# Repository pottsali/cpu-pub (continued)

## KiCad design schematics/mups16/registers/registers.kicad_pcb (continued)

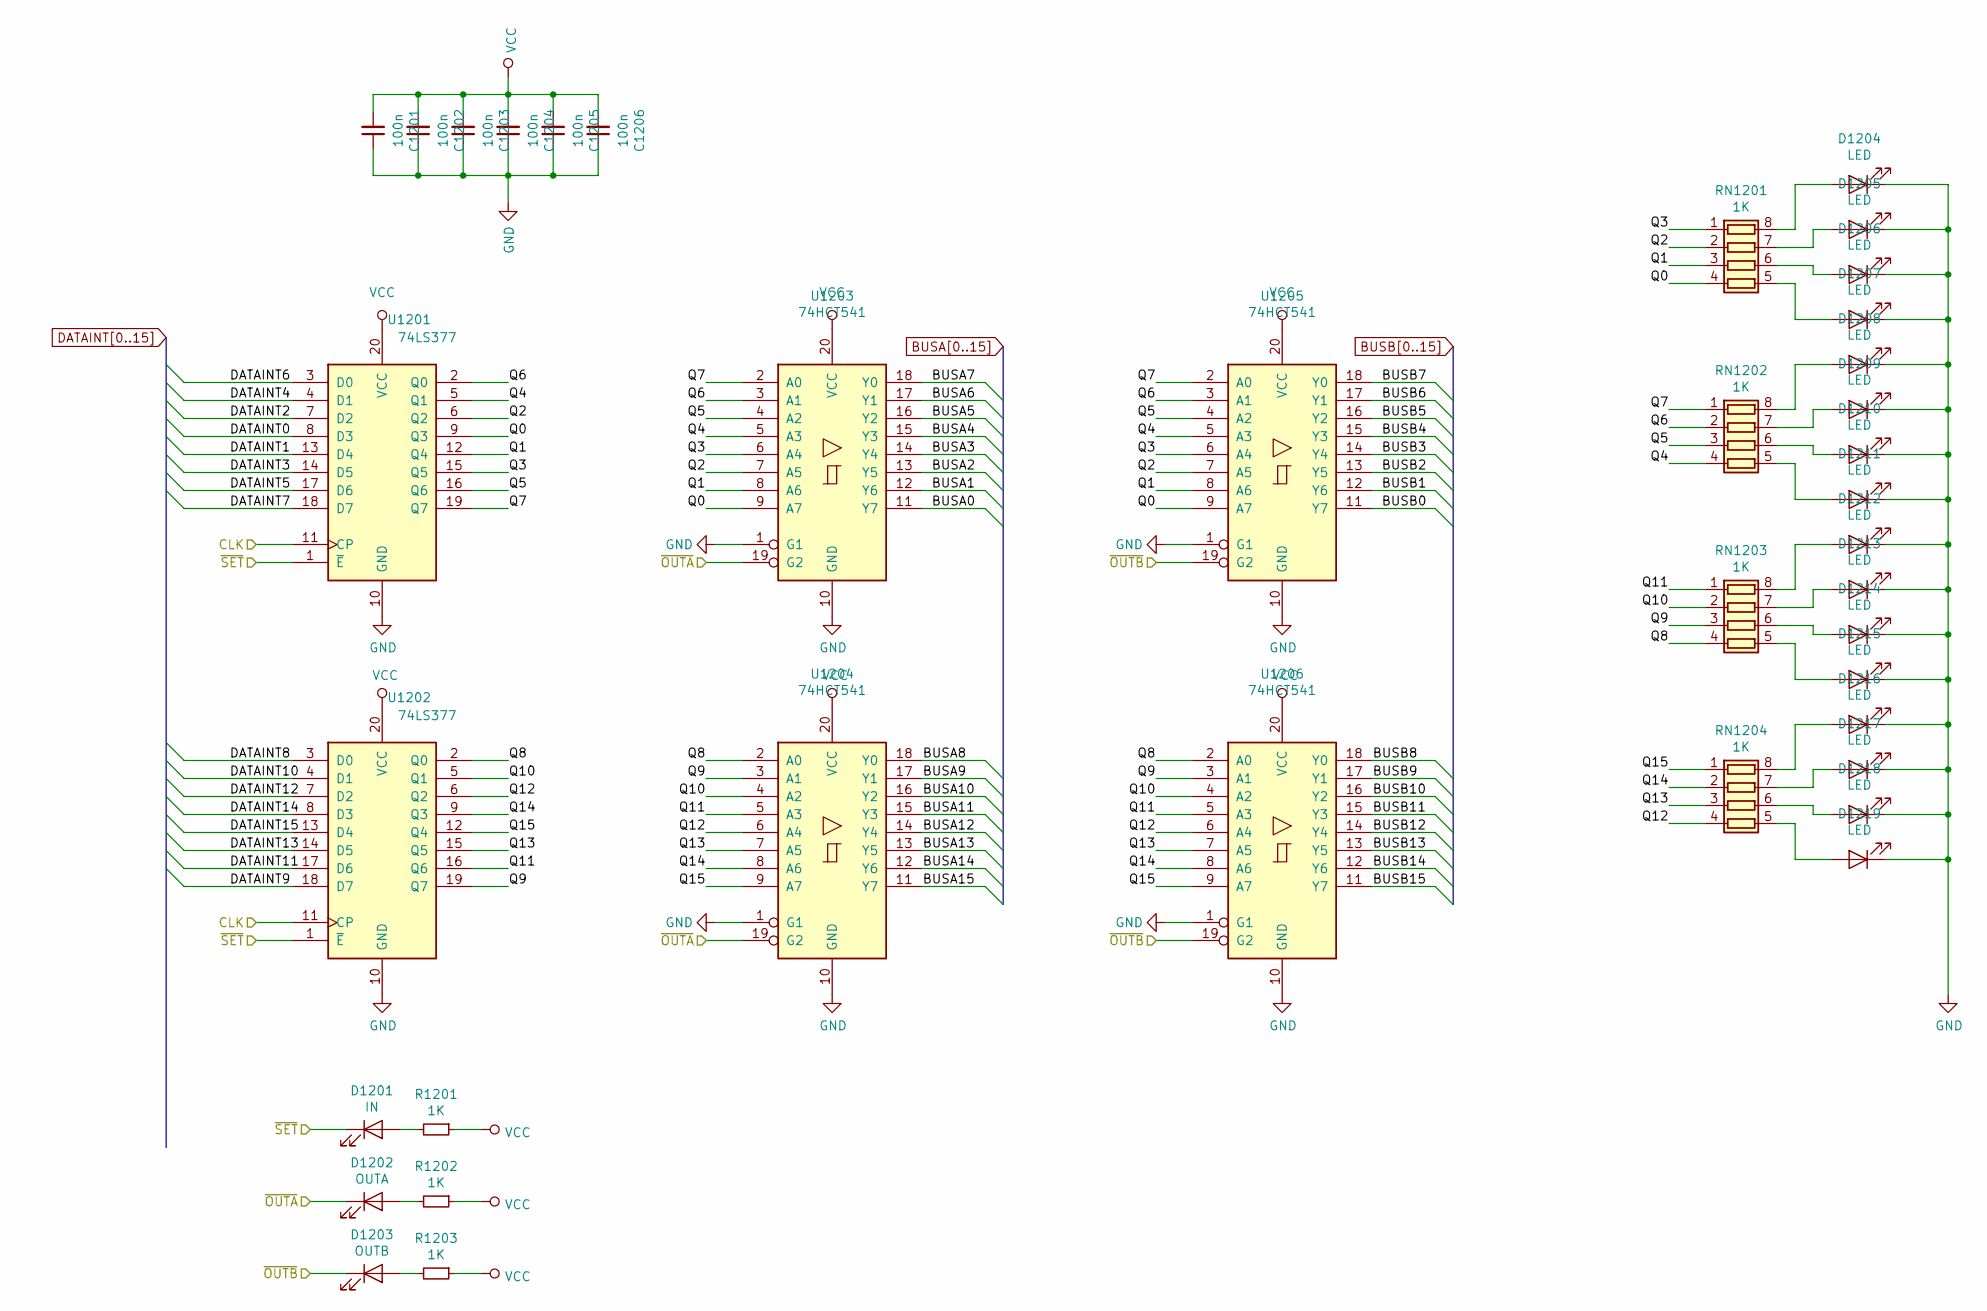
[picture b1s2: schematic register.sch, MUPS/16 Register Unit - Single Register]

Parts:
C201, C202, C203, C204, C205, C206: 100n; C_0805_2012Metric
D201: IN; LED_0805_2012Metric
D202: OUTA; LED_0805_2012Metric
D203: OUTB; LED_0805_2012Metric
D204, D205, D206, D207, D208, D209, D210, D211, D212, D213, D214, D215, D216, D217, D218, D219: LED; LED_0805_2012Metric
R201, R202, R203: 1K; R_0805_2012Metric
RN201, RN202, RN203, RN204: 1K; R_Array_Convex_4x1206
U201, U202: 74LS377; SOIC-20W_7.5x12.8mm_P1.27mm
U203, U204, U205, U206: 74HCT541; SOIC-20W_7.5x12.8mm_P1.27mm

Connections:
/CLK: U201.11 (CP), U202.11 (CP); also elsewhere on the board
/OUTA1: D202.1 (K), U203.19 (G2), U204.19 (G2); also elsewhere on the board
/OUTB1: D203.1 (K), U205.19 (G2), U206.19 (G2); also elsewhere on the board
/SETF1: D201.1 (K), U201.1 (~E), U202.1 (~E); also elsewhere on the board
/r1/Q0: RN201.4 (R4.1), U201.9 (Q3), U203.9 (A7), U205.9 (A7)
/r1/Q1: RN201.3 (R3.1), U201.12 (Q4), U203.8 (A6), U205.8 (A6)
/r1/Q2: RN201.2 (R2.1), U201.6 (Q2), U203.7 (A5), U205.7 (A5)
/r1/Q3: RN201.1 (R1.1), U201.15 (Q5), U203.6 (A4), U205.6 (A4)
/r1/Q4: RN202.4 (R4.1), U201.5 (Q1), U203.5 (A3), U205.5 (A3)
/r1/Q5: RN202.3 (R3.1), U201.16 (Q6), U203.4 (A2), U205.4 (A2)
/r1/Q6: RN202.2 (R2.1), U201.2 (Q0), U203.3 (A1), U205.3 (A1)
/r1/Q7: RN202.1 (R1.1), U201.19 (Q7), U203.2 (A0), U205.2 (A0)
/r1/Q8: RN203.4 (R4.1), U202.2 (Q0), U204.2 (A0), U206.2 (A0)
/r1/Q9: RN203.3 (R3.1), U202.19 (Q7), U204.3 (A1), U206.3 (A1)
/r1/Q10: RN203.2 (R2.1), U202.5 (Q1), U204.4 (A2), U206.4 (A2)
/r1/Q11: RN203.1 (R1.1), U202.16 (Q6), U204.5 (A3), U206.5 (A3)
/r1/Q12: RN204.4 (R4.1), U202.6 (Q2), U204.6 (A4), U206.6 (A4)
/r1/Q13: RN204.3 (R3.1), U202.15 (Q5), U204.7 (A5), U206.7 (A5)
/r1/Q14: RN204.2 (R2.1), U202.9 (Q3), U204.8 (A6), U206.8 (A6)
/r1/Q15: RN204.1 (R1.1), U202.12 (Q4), U204.9 (A7), U206.9 (A7)
BUSA0: U203.11 (Y7); also elsewhere on the board
BUSA1: U203.12 (Y6); also elsewhere on the board
BUSA2: U203.13 (Y5); also elsewhere on the board
BUSA3: U203.14 (Y4); also elsewhere on the board
BUSA4: U203.15 (Y3); also elsewhere on the board
BUSA5: U203.16 (Y2); also elsewhere on the board
BUSA6: U203.17 (Y1); also elsewhere on the board
BUSA7: U203.18 (Y0); also elsewhere on the board
BUSA8: U204.18 (Y0); also elsewhere on the board
BUSA9: U204.17 (Y1); also elsewhere on the board
BUSA10: U204.16 (Y2); also elsewhere on the board
BUSA11: U204.15 (Y3); also elsewhere on the board
BUSA12: U204.14 (Y4); also elsewhere on the board
BUSA13: U204.13 (Y5); also elsewhere on the board
BUSA14: U204.12 (Y6); also elsewhere on the board
BUSA15: U204.11 (Y7); also elsewhere on the board
BUSB0: U205.11 (Y7); also elsewhere on the board
BUSB1: U205.12 (Y6); also elsewhere on the board
BUSB2: U205.13 (Y5); also elsewhere on the board
BUSB3: U205.14 (Y4); also elsewhere on the board
BUSB4: U205.15 (Y3); also elsewhere on the board
BUSB5: U205.16 (Y2); also elsewhere on the board
BUSB6: U205.17 (Y1); also elsewhere on the board
BUSB7: U205.18 (Y0); also elsewhere on the board
BUSB8: U206.18 (Y0); also elsewhere on the board
BUSB9: U206.17 (Y1); also elsewhere on the board
BUSB10: U206.16 (Y2); also elsewhere on the board
BUSB11: U206.15 (Y3); also elsewhere on the board
BUSB12: U206.14 (Y4); also elsewhere on the board
BUSB13: U206.13 (Y5); also elsewhere on the board
BUSB14: U206.12 (Y6); also elsewhere on the board
BUSB15: U206.11 (Y7); also elsewhere on the board
DATAINT0: U201.8 (D3); also elsewhere on the board
DATAINT1: U201.13 (D4); also elsewhere on the board
DATAINT2: U201.7 (D2); also elsewhere on the board
DATAINT3: U201.14 (D5); also elsewhere on the board
DATAINT4: U201.4 (D1); also elsewhere on the board
DATAINT5: U201.17 (D6); also elsewhere on the board
DATAINT6: U201.3 (D0); also elsewhere on the board
DATAINT7: U201.18 (D7); also elsewhere on the board
DATAINT8: U202.3 (D0); also elsewhere on the board
DATAINT9: U202.18 (D7); also elsewhere on the board
DATAINT10: U202.4 (D1); also elsewhere on the board
DATAINT11: U202.17 (D6); also elsewhere on the board
DATAINT12: U202.7 (D2); also elsewhere on the board
DATAINT13: U202.14 (D5); also elsewhere on the board
DATAINT14: U202.8 (D3); also elsewhere on the board
DATAINT15: U202.13 (D4); also elsewhere on the board
GND: C201.1, C202.1, C203.1, C204.1, C205.1, C206.1, D204.1 (K), D205.1 (K), D206.1 (K), D207.1 (K), D208.1 (K), D209.1 (K), D210.1 (K), D211.1 (K), D212.1 (K), D213.1 (K), D214.1 (K), D215.1 (K), D216.1 (K), D217.1 (K), D218.1 (K), D219.1 (K), U201.10 (GND), U202.10 (GND), U203.1 (G1), U203.10 (GND), U204.1 (G1), U204.10 (GND), U205.1 (G1), U205.10 (GND), U206.1 (G1), U206.10 (GND); also elsewhere on the board
unnamed: D201.2 (A), R201.2
unnamed: D202.2 (A), R202.2
unnamed: D203.2 (A), R203.2
unnamed: D204.2 (A), RN201.8 (R1.2)
unnamed: D205.2 (A), RN201.7 (R2.2)
unnamed: D206.2 (A), RN201.6 (R3.2)
unnamed: D207.2 (A), RN201.5 (R4.2)
unnamed: D208.2 (A), RN202.8 (R1.2)
unnamed: D209.2 (A), RN202.7 (R2.2)
unnamed: D210.2 (A), RN202.6 (R3.2)
unnamed: D211.2 (A), RN202.5 (R4.2)
unnamed: D212.2 (A), RN203.8 (R1.2)
unnamed: D213.2 (A), RN203.7 (R2.2)
unnamed: D214.2 (A), RN203.6 (R3.2)
unnamed: D215.2 (A), RN203.5 (R4.2)
unnamed: D216.2 (A), RN204.8 (R1.2)
unnamed: D217.2 (A), RN204.7 (R2.2)
unnamed: D218.2 (A), RN204.6 (R3.2)
unnamed: D219.2 (A), RN204.5 (R4.2)
VCC: C201.2, C202.2, C203.2, C204.2, C205.2, C206.2, R201.1, R202.1, R203.1, U201.20 (VCC), U202.20 (VCC), U203.20 (VCC), U204.20 (VCC), U205.20 (VCC), U206.20 (VCC); also elsewhere on the board

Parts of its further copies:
C301, C302, C303, C304, C305, C306, C401, C402, C403, C404, C405, C406, C501, C502, C503, C504, C505, C506, C601, C602, C603, C604, C605, C606, C701, C702, C703, C704, C705, C706, C801, C802, C803, C804, C805, C806, C901, C902, C903, C904, C905, C906, C1001, C1002, C1003, C1004, C1005, C1006, C1101, C1102, C1103, C1104, C1105, C1106, C1201, C1202, C1203, C1204, C1205, C1206, C1301, C1302, C1303, C1304, C1305, C1306, C1401, C1402, C1403, C1404, C1405, C1406: 100n; C_0805_2012Metric
D301, D401, D501, D601, D701, D801, D901, D1001, D1101, D1201, D1301, D1401: IN; LED_0805_2012Metric
D302, D402, D502, D602, D702, D802, D902, D1002, D1102, D1202, D1302, D1402: OUTA; LED_0805_2012Metric
D303, D403, D503, D603, D703, D803, D903, D1003, D1103, D1203, D1303, D1403: OUTB; LED_0805_2012Metric
D304, D305, D306, D307, D308, D309, D310, D311, D312, D313, D314, D315, D316, D317, D318, D319, D404, D405, D406, D407, D408, D409, D410, D411, D412, D413, D414, D415, D416, D417, D418, D419, D504, D505, D506, D507, D508, D509, D510, D511, D512, D513, D514, D515, D516, D517, D518, D519, D604, D605, D606, D607, D608, D609, D610, D611, D612, D613, D614, D615, D616, D617, D618, D619, D704, D705, D706, D707, D708, D709, D710, D711, D712, D713, D714, D715, D716, D717, D718, D719, D804, D805, D806, D807, D808, D809, D810, D811, D812, D813, D814, D815, D816, D817, D818, D819, D904, D905, D906, D907, D908, D909, D910, D911, D912, D913, D914, D915, D916, D917, D918, D919, D1004, D1005, D1006, D1007, D1008, D1009, D1010, D1011, D1012, D1013, D1014, D1015, D1016, D1017, D1018, D1019, D1104, D1105, D1106, D1107, D1108, D1109, D1110, D1111, D1112, D1113, D1114, D1115, D1116, D1117, D1118, D1119, D1204, D1205, D1206, D1207, D1208, D1209, D1210, D1211, D1212, D1213, D1214, D1215, D1216, D1217, D1218, D1219, D1304, D1305, D1306, D1307, D1308, D1309, D1310, D1311, D1312, D1313, D1314, D1315, D1316, D1317, D1318, D1319, D1404, D1405, D1406, D1407, D1408, D1409, D1410, D1411, D1412, D1413, D1414, D1415, D1416, D1417, D1418, D1419: LED; LED_0805_2012Metric
R301, R302, R303, R401, R402, R403, R501, R502, R503, R601, R602, R603, R701, R702, R703, R801, R802, R803, R901, R902, R903, R1001, R1002, R1003, R1101, R1102, R1103, R1201, R1202, R1203, R1301, R1302, R1303, R1401, R1402, R1403: 1K; R_0805_2012Metric
RN301, RN302, RN303, RN304, RN401, RN402, RN403, RN404, RN501, RN502, RN503, RN504, RN601, RN602, RN603, RN604, RN701, RN702, RN703, RN704, RN801, RN802, RN803, RN804, RN901, RN902, RN903, RN904, RN1001, RN1002, RN1003, RN1004, RN1101, RN1102, RN1103, RN1104, RN1201, RN1202, RN1203, RN1204, RN1301, RN1302, RN1303, RN1304, RN1401, RN1402, RN1403, RN1404: 1K; R_Array_Convex_4x1206
U301, U302, U401, U402, U501, U502, U601, U602, U701, U702, U801, U802, U901, U902, U1001, U1002, U1101, U1102, U1201, U1202, U1301, U1302, U1401, U1402: 74LS377; SOIC-20W_7.5x12.8mm_P1.27mm
U303, U304, U305, U306, U403, U404, U405, U406, U503, U504, U505, U506, U603, U604, U605, U606, U703, U704, U705, U706, U803, U804, U805, U806, U903, U904, U905, U906, U1003, U1004, U1005, U1006, U1103, U1104, U1105, U1106, U1203, U1204, U1205, U1206, U1303, U1304, U1305, U1306, U1403, U1404, U1405, U1406: 74HCT541; SOIC-20W_7.5x12.8mm_P1.27mm

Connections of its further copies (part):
/CLK: U301.11 (CP), U302.11 (CP), U401.11 (CP), U402.11 (CP), U501.11 (CP), U502.11 (CP), U601.11 (CP), U602.11 (CP), U701.11 (CP), U702.11 (CP), U801.11 (CP), U802.11 (CP), U901.11 (CP), U902.11 (CP), U1001.11 (CP), U1002.11 (CP), U1101.11 (CP), U1102.11 (CP), U1201.11 (CP), U1202.11 (CP), U1301.11 (CP), U1302.11 (CP), U1401.11 (CP), U1402.11 (CP); also elsewhere on the board
/OUTA2: D302.1 (K), U303.19 (G2), U304.19 (G2); also elsewhere on the board
/OUTA3: D1102.1 (K), U1103.19 (G2), U1104.19 (G2); also elsewhere on the board
/OUTA4: D1202.1 (K), U1203.19 (G2), U1204.19 (G2); also elsewhere on the board
/OUTA5: D402.1 (K), U403.19 (G2), U404.19 (G2); also elsewhere on the board
/OUTA6: D502.1 (K), U503.19 (G2), U504.19 (G2); also elsewhere on the board
/OUTA7: D602.1 (K), U603.19 (G2), U604.19 (G2); also elsewhere on the board
/OUTA8: D702.1 (K), U703.19 (G2), U704.19 (G2); also elsewhere on the board
/OUTA9: D802.1 (K), U803.19 (G2), U804.19 (G2); also elsewhere on the board
/OUTA10: D902.1 (K), U903.19 (G2), U904.19 (G2); also elsewhere on the board
/OUTA11: D1002.1 (K), U1003.19 (G2), U1004.19 (G2); also elsewhere on the board
/OUTA12: D1302.1 (K), U1303.19 (G2), U1304.19 (G2); also elsewhere on the board
/OUTA13: D1402.1 (K), U1403.19 (G2), U1404.19 (G2); also elsewhere on the board
/OUTB2: D303.1 (K), U305.19 (G2), U306.19 (G2); also elsewhere on the board
/OUTB3: D1103.1 (K), U1105.19 (G2), U1106.19 (G2); also elsewhere on the board
/OUTB4: D1203.1 (K), U1205.19 (G2), U1206.19 (G2); also elsewhere on the board
/OUTB5: D403.1 (K), U405.19 (G2), U406.19 (G2); also elsewhere on the board
/OUTB6: D503.1 (K), U505.19 (G2), U506.19 (G2); also elsewhere on the board
/OUTB7: D603.1 (K), U605.19 (G2), U606.19 (G2); also elsewhere on the board
/OUTB8: D703.1 (K), U705.19 (G2), U706.19 (G2); also elsewhere on the board
/OUTB9: D803.1 (K), U805.19 (G2), U806.19 (G2); also elsewhere on the board
/OUTB10: D903.1 (K), U905.19 (G2), U906.19 (G2); also elsewhere on the board
/OUTB11: D1003.1 (K), U1005.19 (G2), U1006.19 (G2); also elsewhere on the board
/OUTB12: D1303.1 (K), U1305.19 (G2), U1306.19 (G2); also elsewhere on the board
/OUTB13: D1403.1 (K), U1405.19 (G2), U1406.19 (G2); also elsewhere on the board
/SETF2: D301.1 (K), U301.1 (~E), U302.1 (~E); also elsewhere on the board
/SETF3: D1101.1 (K), U1101.1 (~E), U1102.1 (~E); also elsewhere on the board
/SETF4: D1201.1 (K), U1201.1 (~E), U1202.1 (~E); also elsewhere on the board
/SETF5: D401.1 (K), U401.1 (~E), U402.1 (~E); also elsewhere on the board
/SETF6: D501.1 (K), U501.1 (~E), U502.1 (~E); also elsewhere on the board
/SETF7: D601.1 (K), U601.1 (~E), U602.1 (~E); also elsewhere on the board
/SETF8: D701.1 (K), U701.1 (~E), U702.1 (~E); also elsewhere on the board
/SETF9: D801.1 (K), U801.1 (~E), U802.1 (~E); also elsewhere on the board
/SETF10: D901.1 (K), U901.1 (~E), U902.1 (~E); also elsewhere on the board
/SETF11: D1001.1 (K), U1001.1 (~E), U1002.1 (~E); also elsewhere on the board
/SETF12: D1301.1 (K), U1301.1 (~E), U1302.1 (~E); also elsewhere on the board
/SETF13: D1401.1 (K), U1401.1 (~E), U1402.1 (~E); also elsewhere on the board
/pc/Q0: RN501.4 (R4.1), U501.9 (Q3), U503.9 (A7), U505.9 (A7)
/pc/Q1: RN501.3 (R3.1), U501.12 (Q4), U503.8 (A6), U505.8 (A6)
/pc/Q2: RN501.2 (R2.1), U501.6 (Q2), U503.7 (A5), U505.7 (A5)
/pc/Q3: RN501.1 (R1.1), U501.15 (Q5), U503.6 (A4), U505.6 (A4)
/pc/Q4: RN502.4 (R4.1), U501.5 (Q1), U503.5 (A3), U505.5 (A3)
/pc/Q5: RN502.3 (R3.1), U501.16 (Q6), U503.4 (A2), U505.4 (A2)
/pc/Q6: RN502.2 (R2.1), U501.2 (Q0), U503.3 (A1), U505.3 (A1)
/pc/Q7: RN502.1 (R1.1), U501.19 (Q7), U503.2 (A0), U505.2 (A0)
/pc/Q8: RN503.4 (R4.1), U502.2 (Q0), U504.2 (A0), U506.2 (A0)
/pc/Q9: RN503.3 (R3.1), U502.19 (Q7), U504.3 (A1), U506.3 (A1)
/pc/Q10: RN503.2 (R2.1), U502.5 (Q1), U504.4 (A2), U506.4 (A2)
/pc/Q11: RN503.1 (R1.1), U502.16 (Q6), U504.5 (A3), U506.5 (A3)
/pc/Q12: RN504.4 (R4.1), U502.6 (Q2), U504.6 (A4), U506.6 (A4)
/pc/Q13: RN504.3 (R3.1), U502.15 (Q5), U504.7 (A5), U506.7 (A5)
/pc/Q14: RN504.2 (R2.1), U502.9 (Q3), U504.8 (A6), U506.8 (A6)
/pc/Q15: RN504.1 (R1.1), U502.12 (Q4), U504.9 (A7), U506.9 (A7)
/r2/Q0: RN301.4 (R4.1), U301.9 (Q3), U303.9 (A7), U305.9 (A7)
/r2/Q1: RN301.3 (R3.1), U301.12 (Q4), U303.8 (A6), U305.8 (A6)
/r2/Q2: RN301.2 (R2.1), U301.6 (Q2), U303.7 (A5), U305.7 (A5)
/r2/Q3: RN301.1 (R1.1), U301.15 (Q5), U303.6 (A4), U305.6 (A4)
/r2/Q4: RN302.4 (R4.1), U301.5 (Q1), U303.5 (A3), U305.5 (A3)
/r2/Q5: RN302.3 (R3.1), U301.16 (Q6), U303.4 (A2), U305.4 (A2)
/r2/Q6: RN302.2 (R2.1), U301.2 (Q0), U303.3 (A1), U305.3 (A1)
/r2/Q7: RN302.1 (R1.1), U301.19 (Q7), U303.2 (A0), U305.2 (A0)
/r2/Q8: RN303.4 (R4.1), U302.2 (Q0), U304.2 (A0), U306.2 (A0)
/r2/Q9: RN303.3 (R3.1), U302.19 (Q7), U304.3 (A1), U306.3 (A1)
/r2/Q10: RN303.2 (R2.1), U302.5 (Q1), U304.4 (A2), U306.4 (A2)
/r2/Q11: RN303.1 (R1.1), U302.16 (Q6), U304.5 (A3), U306.5 (A3)
/r2/Q12: RN304.4 (R4.1), U302.6 (Q2), U304.6 (A4), U306.6 (A4)
/r2/Q13: RN304.3 (R3.1), U302.15 (Q5), U304.7 (A5), U306.7 (A5)
/r2/Q14: RN304.2 (R2.1), U302.9 (Q3), U304.8 (A6), U306.8 (A6)
/r2/Q15: RN304.1 (R1.1), U302.12 (Q4), U304.9 (A7), U306.9 (A7)
/r3/Q0: RN1101.4 (R4.1), U1101.9 (Q3), U1103.9 (A7), U1105.9 (A7)
/r3/Q1: RN1101.3 (R3.1), U1101.12 (Q4), U1103.8 (A6), U1105.8 (A6)
/r3/Q2: RN1101.2 (R2.1), U1101.6 (Q2), U1103.7 (A5), U1105.7 (A5)
/r3/Q3: RN1101.1 (R1.1), U1101.15 (Q5), U1103.6 (A4), U1105.6 (A4)
/r3/Q4: RN1102.4 (R4.1), U1101.5 (Q1), U1103.5 (A3), U1105.5 (A3)
/r3/Q5: RN1102.3 (R3.1), U1101.16 (Q6), U1103.4 (A2), U1105.4 (A2)
/r3/Q6: RN1102.2 (R2.1), U1101.2 (Q0), U1103.3 (A1), U1105.3 (A1)
/r3/Q7: RN1102.1 (R1.1), U1101.19 (Q7), U1103.2 (A0), U1105.2 (A0)
/r3/Q8: RN1103.4 (R4.1), U1102.2 (Q0), U1104.2 (A0), U1106.2 (A0)
/r3/Q9: RN1103.3 (R3.1), U1102.19 (Q7), U1104.3 (A1), U1106.3 (A1)
/r3/Q10: RN1103.2 (R2.1), U1102.5 (Q1), U1104.4 (A2), U1106.4 (A2)
/r3/Q11: RN1103.1 (R1.1), U1102.16 (Q6), U1104.5 (A3), U1106.5 (A3)
/r3/Q12: RN1104.4 (R4.1), U1102.6 (Q2), U1104.6 (A4), U1106.6 (A4)
/r3/Q13: RN1104.3 (R3.1), U1102.15 (Q5), U1104.7 (A5), U1106.7 (A5)
/r3/Q14: RN1104.2 (R2.1), U1102.9 (Q3), U1104.8 (A6), U1106.8 (A6)
/r3/Q15: RN1104.1 (R1.1), U1102.12 (Q4), U1104.9 (A7), U1106.9 (A7)
/r4/Q0: RN1201.4 (R4.1), U1201.9 (Q3), U1203.9 (A7), U1205.9 (A7)
/r4/Q1: RN1201.3 (R3.1), U1201.12 (Q4), U1203.8 (A6), U1205.8 (A6)
/r4/Q2: RN1201.2 (R2.1), U1201.6 (Q2), U1203.7 (A5), U1205.7 (A5)
/r4/Q3: RN1201.1 (R1.1), U1201.15 (Q5), U1203.6 (A4), U1205.6 (A4)
/r4/Q4: RN1202.4 (R4.1), U1201.5 (Q1), U1203.5 (A3), U1205.5 (A3)
/r4/Q5: RN1202.3 (R3.1), U1201.16 (Q6), U1203.4 (A2), U1205.4 (A2)
/r4/Q6: RN1202.2 (R2.1), U1201.2 (Q0), U1203.3 (A1), U1205.3 (A1)
/r4/Q7: RN1202.1 (R1.1), U1201.19 (Q7), U1203.2 (A0), U1205.2 (A0)
/r4/Q8: RN1203.4 (R4.1), U1202.2 (Q0), U1204.2 (A0), U1206.2 (A0)
/r4/Q9: RN1203.3 (R3.1), U1202.19 (Q7), U1204.3 (A1), U1206.3 (A1)
/r4/Q10: RN1203.2 (R2.1), U1202.5 (Q1), U1204.4 (A2), U1206.4 (A2)
/r4/Q11: RN1203.1 (R1.1), U1202.16 (Q6), U1204.5 (A3), U1206.5 (A3)
/r4/Q12: RN1204.4 (R4.1), U1202.6 (Q2), U1204.6 (A4), U1206.6 (A4)
/r4/Q13: RN1204.3 (R3.1), U1202.15 (Q5), U1204.7 (A5), U1206.7 (A5)
/r4/Q14: RN1204.2 (R2.1), U1202.9 (Q3), U1204.8 (A6), U1206.8 (A6)
/r4/Q15: RN1204.1 (R1.1), U1202.12 (Q4), U1204.9 (A7), U1206.9 (A7)
/ra/Q0: RN601.4 (R4.1), U601.9 (Q3), U603.9 (A7), U605.9 (A7)
/ra/Q1: RN601.3 (R3.1), U601.12 (Q4), U603.8 (A6), U605.8 (A6)
/ra/Q2: RN601.2 (R2.1), U601.6 (Q2), U603.7 (A5), U605.7 (A5)
/ra/Q3: RN601.1 (R1.1), U601.15 (Q5), U603.6 (A4), U605.6 (A4)
/ra/Q4: RN602.4 (R4.1), U601.5 (Q1), U603.5 (A3), U605.5 (A3)
/ra/Q5: RN602.3 (R3.1), U601.16 (Q6), U603.4 (A2), U605.4 (A2)
/ra/Q6: RN602.2 (R2.1), U601.2 (Q0), U603.3 (A1), U605.3 (A1)
/ra/Q7: RN602.1 (R1.1), U601.19 (Q7), U603.2 (A0), U605.2 (A0)
/ra/Q8: RN603.4 (R4.1), U602.2 (Q0), U604.2 (A0), U606.2 (A0)
/ra/Q9: RN603.3 (R3.1), U602.19 (Q7), U604.3 (A1), U606.3 (A1)
/ra/Q10: RN603.2 (R2.1), U602.5 (Q1), U604.4 (A2), U606.4 (A2)
/ra/Q11: RN603.1 (R1.1), U602.16 (Q6), U604.5 (A3), U606.5 (A3)
/ra/Q12: RN604.4 (R4.1), U602.6 (Q2), U604.6 (A4), U606.6 (A4)
/ra/Q13: RN604.3 (R3.1), U602.15 (Q5), U604.7 (A5), U606.7 (A5)
/ra/Q14: RN604.2 (R2.1), U602.9 (Q3), U604.8 (A6), U606.8 (A6)
/ra/Q15: RN604.1 (R1.1), U602.12 (Q4), U604.9 (A7), U606.9 (A7)
/s1/Q0: RN801.4 (R4.1), U801.9 (Q3), U803.9 (A7), U805.9 (A7)
/s1/Q1: RN801.3 (R3.1), U801.12 (Q4), U803.8 (A6), U805.8 (A6)
/s1/Q2: RN801.2 (R2.1), U801.6 (Q2), U803.7 (A5), U805.7 (A5)
/s1/Q3: RN801.1 (R1.1), U801.15 (Q5), U803.6 (A4), U805.6 (A4)
/s1/Q4: RN802.4 (R4.1), U801.5 (Q1), U803.5 (A3), U805.5 (A3)
/s1/Q5: RN802.3 (R3.1), U801.16 (Q6), U803.4 (A2), U805.4 (A2)
/s1/Q6: RN802.2 (R2.1), U801.2 (Q0), U803.3 (A1), U805.3 (A1)
/s1/Q7: RN802.1 (R1.1), U801.19 (Q7), U803.2 (A0), U805.2 (A0)
/s1/Q8: RN803.4 (R4.1), U802.2 (Q0), U804.2 (A0), U806.2 (A0)
/s1/Q9: RN803.3 (R3.1), U802.19 (Q7), U804.3 (A1), U806.3 (A1)
/s1/Q10: RN803.2 (R2.1), U802.5 (Q1), U804.4 (A2), U806.4 (A2)
/s1/Q11: RN803.1 (R1.1), U802.16 (Q6), U804.5 (A3), U806.5 (A3)
/s1/Q12: RN804.4 (R4.1), U802.6 (Q2), U804.6 (A4), U806.6 (A4)
/s1/Q13: RN804.3 (R3.1), U802.15 (Q5), U804.7 (A5), U806.7 (A5)
/s1/Q14: RN804.2 (R2.1), U802.9 (Q3), U804.8 (A6), U806.8 (A6)
/s1/Q15: RN804.1 (R1.1), U802.12 (Q4), U804.9 (A7), U806.9 (A7)
/s2/Q0: RN901.4 (R4.1), U901.9 (Q3), U903.9 (A7), U905.9 (A7)
/s2/Q1: RN901.3 (R3.1), U901.12 (Q4), U903.8 (A6), U905.8 (A6)
/s2/Q2: RN901.2 (R2.1), U901.6 (Q2), U903.7 (A5), U905.7 (A5)
/s2/Q3: RN901.1 (R1.1), U901.15 (Q5), U903.6 (A4), U905.6 (A4)
/s2/Q4: RN902.4 (R4.1), U901.5 (Q1), U903.5 (A3), U905.5 (A3)
/s2/Q5: RN902.3 (R3.1), U901.16 (Q6), U903.4 (A2), U905.4 (A2)
/s2/Q6: RN902.2 (R2.1), U901.2 (Q0), U903.3 (A1), U905.3 (A1)
/s2/Q7: RN902.1 (R1.1), U901.19 (Q7), U903.2 (A0), U905.2 (A0)
/s2/Q8: RN903.4 (R4.1), U902.2 (Q0), U904.2 (A0), U906.2 (A0)
/s2/Q9: RN903.3 (R3.1), U902.19 (Q7), U904.3 (A1), U906.3 (A1)
/s2/Q10: RN903.2 (R2.1), U902.5 (Q1), U904.4 (A2), U906.4 (A2)
/s2/Q11: RN903.1 (R1.1), U902.16 (Q6), U904.5 (A3), U906.5 (A3)
/s2/Q12: RN904.4 (R4.1), U902.6 (Q2), U904.6 (A4), U906.6 (A4)
/s2/Q13: RN904.3 (R3.1), U902.15 (Q5), U904.7 (A5), U906.7 (A5)
/s2/Q14: RN904.2 (R2.1), U902.9 (Q3), U904.8 (A6), U906.8 (A6)
/s2/Q15: RN904.1 (R1.1), U902.12 (Q4), U904.9 (A7), U906.9 (A7)
/s3/Q0: RN1001.4 (R4.1), U1001.9 (Q3), U1003.9 (A7), U1005.9 (A7)
/s3/Q1: RN1001.3 (R3.1), U1001.12 (Q4), U1003.8 (A6), U1005.8 (A6)
/s3/Q2: RN1001.2 (R2.1), U1001.6 (Q2), U1003.7 (A5), U1005.7 (A5)
/s3/Q3: RN1001.1 (R1.1), U1001.15 (Q5), U1003.6 (A4), U1005.6 (A4)
/s3/Q4: RN1002.4 (R4.1), U1001.5 (Q1), U1003.5 (A3), U1005.5 (A3)
/s3/Q5: RN1002.3 (R3.1), U1001.16 (Q6), U1003.4 (A2), U1005.4 (A2)
/s3/Q6: RN1002.2 (R2.1), U1001.2 (Q0), U1003.3 (A1), U1005.3 (A1)
/s3/Q7: RN1002.1 (R1.1), U1001.19 (Q7), U1003.2 (A0), U1005.2 (A0)
/s3/Q8: RN1003.4 (R4.1), U1002.2 (Q0), U1004.2 (A0), U1006.2 (A0)
/s3/Q9: RN1003.3 (R3.1), U1002.19 (Q7), U1004.3 (A1), U1006.3 (A1)
/s3/Q10: RN1003.2 (R2.1), U1002.5 (Q1), U1004.4 (A2), U1006.4 (A2)
/s3/Q11: RN1003.1 (R1.1), U1002.16 (Q6), U1004.5 (A3), U1006.5 (A3)
/s3/Q12: RN1004.4 (R4.1), U1002.6 (Q2), U1004.6 (A4), U1006.6 (A4)
/s3/Q13: RN1004.3 (R3.1), U1002.15 (Q5), U1004.7 (A5), U1006.7 (A5)
/s3/Q14: RN1004.2 (R2.1), U1002.9 (Q3), U1004.8 (A6), U1006.8 (A6)
/s3/Q15: RN1004.1 (R1.1), U1002.12 (Q4), U1004.9 (A7), U1006.9 (A7)
/sp/Q0: RN401.4 (R4.1), U401.9 (Q3), U403.9 (A7), U405.9 (A7)
/sp/Q1: RN401.3 (R3.1), U401.12 (Q4), U403.8 (A6), U405.8 (A6)
/sp/Q2: RN401.2 (R2.1), U401.6 (Q2), U403.7 (A5), U405.7 (A5)
/sp/Q3: RN401.1 (R1.1), U401.15 (Q5), U403.6 (A4), U405.6 (A4)
/sp/Q4: RN402.4 (R4.1), U401.5 (Q1), U403.5 (A3), U405.5 (A3)
/sp/Q5: RN402.3 (R3.1), U401.16 (Q6), U403.4 (A2), U405.4 (A2)
/sp/Q6: RN402.2 (R2.1), U401.2 (Q0), U403.3 (A1), U405.3 (A1)
/sp/Q7: RN402.1 (R1.1), U401.19 (Q7), U403.2 (A0), U405.2 (A0)
/sp/Q8: RN403.4 (R4.1), U402.2 (Q0), U404.2 (A0), U406.2 (A0)
/sp/Q9: RN403.3 (R3.1), U402.19 (Q7), U404.3 (A1), U406.3 (A1)
/sp/Q10: RN403.2 (R2.1), U402.5 (Q1), U404.4 (A2), U406.4 (A2)
/sp/Q11: RN403.1 (R1.1), U402.16 (Q6), U404.5 (A3), U406.5 (A3)
/sp/Q12: RN404.4 (R4.1), U402.6 (Q2), U404.6 (A4), U406.6 (A4)
/sp/Q13: RN404.3 (R3.1), U402.15 (Q5), U404.7 (A5), U406.7 (A5)
/sp/Q14: RN404.2 (R2.1), U402.9 (Q3), U404.8 (A6), U406.8 (A6)
/sp/Q15: RN404.1 (R1.1), U402.12 (Q4), U404.9 (A7), U406.9 (A7)
/spc/Q0: RN701.4 (R4.1), U701.9 (Q3), U703.9 (A7), U705.9 (A7)
/spc/Q1: RN701.3 (R3.1), U701.12 (Q4), U703.8 (A6), U705.8 (A6)
/spc/Q2: RN701.2 (R2.1), U701.6 (Q2), U703.7 (A5), U705.7 (A5)
/spc/Q3: RN701.1 (R1.1), U701.15 (Q5), U703.6 (A4), U705.6 (A4)
/spc/Q4: RN702.4 (R4.1), U701.5 (Q1), U703.5 (A3), U705.5 (A3)
/spc/Q5: RN702.3 (R3.1), U701.16 (Q6), U703.4 (A2), U705.4 (A2)
/spc/Q6: RN702.2 (R2.1), U701.2 (Q0), U703.3 (A1), U705.3 (A1)
/spc/Q7: RN702.1 (R1.1), U701.19 (Q7), U703.2 (A0), U705.2 (A0)
/spc/Q8: RN703.4 (R4.1), U702.2 (Q0), U704.2 (A0), U706.2 (A0)
/spc/Q9: RN703.3 (R3.1), U702.19 (Q7), U704.3 (A1), U706.3 (A1)
/spc/Q10: RN703.2 (R2.1), U702.5 (Q1), U704.4 (A2), U706.4 (A2)
/spc/Q11: RN703.1 (R1.1), U702.16 (Q6), U704.5 (A3), U706.5 (A3)
/spc/Q12: RN704.4 (R4.1), U702.6 (Q2), U704.6 (A4), U706.6 (A4)
/spc/Q13: RN704.3 (R3.1), U702.15 (Q5), U704.7 (A5), U706.7 (A5)
/spc/Q14: RN704.2 (R2.1), U702.9 (Q3), U704.8 (A6), U706.8 (A6)
/spc/Q15: RN704.1 (R1.1), U702.12 (Q4), U704.9 (A7), U706.9 (A7)
/temp/Q0: RN1401.4 (R4.1), U1401.9 (Q3), U1403.9 (A7), U1405.9 (A7)
/temp/Q1: RN1401.3 (R3.1), U1401.12 (Q4), U1403.8 (A6), U1405.8 (A6)
/temp/Q2: RN1401.2 (R2.1), U1401.6 (Q2), U1403.7 (A5), U1405.7 (A5)
/temp/Q3: RN1401.1 (R1.1), U1401.15 (Q5), U1403.6 (A4), U1405.6 (A4)
/temp/Q4: RN1402.4 (R4.1), U1401.5 (Q1), U1403.5 (A3), U1405.5 (A3)
/temp/Q5: RN1402.3 (R3.1), U1401.16 (Q6), U1403.4 (A2), U1405.4 (A2)
/temp/Q6: RN1402.2 (R2.1), U1401.2 (Q0), U1403.3 (A1), U1405.3 (A1)
/temp/Q7: RN1402.1 (R1.1), U1401.19 (Q7), U1403.2 (A0), U1405.2 (A0)
/temp/Q8: RN1403.4 (R4.1), U1402.2 (Q0), U1404.2 (A0), U1406.2 (A0)
/temp/Q9: RN1403.3 (R3.1), U1402.19 (Q7), U1404.3 (A1), U1406.3 (A1)
/temp/Q10: RN1403.2 (R2.1), U1402.5 (Q1), U1404.4 (A2), U1406.4 (A2)
/temp/Q11: RN1403.1 (R1.1), U1402.16 (Q6), U1404.5 (A3), U1406.5 (A3)
/temp/Q12: RN1404.4 (R4.1), U1402.6 (Q2), U1404.6 (A4), U1406.6 (A4)
/temp/Q13: RN1404.3 (R3.1), U1402.15 (Q5), U1404.7 (A5), U1406.7 (A5)
/temp/Q14: RN1404.2 (R2.1), U1402.9 (Q3), U1404.8 (A6), U1406.8 (A6)
/temp/Q15: RN1404.1 (R1.1), U1402.12 (Q4), U1404.9 (A7), U1406.9 (A7)
/tsp/Q0: RN1301.4 (R4.1), U1301.9 (Q3), U1303.9 (A7), U1305.9 (A7)
/tsp/Q1: RN1301.3 (R3.1), U1301.12 (Q4), U1303.8 (A6), U1305.8 (A6)
/tsp/Q2: RN1301.2 (R2.1), U1301.6 (Q2), U1303.7 (A5), U1305.7 (A5)
/tsp/Q3: RN1301.1 (R1.1), U1301.15 (Q5), U1303.6 (A4), U1305.6 (A4)
/tsp/Q4: RN1302.4 (R4.1), U1301.5 (Q1), U1303.5 (A3), U1305.5 (A3)
/tsp/Q5: RN1302.3 (R3.1), U1301.16 (Q6), U1303.4 (A2), U1305.4 (A2)
/tsp/Q6: RN1302.2 (R2.1), U1301.2 (Q0), U1303.3 (A1), U1305.3 (A1)
/tsp/Q7: RN1302.1 (R1.1), U1301.19 (Q7), U1303.2 (A0), U1305.2 (A0)
/tsp/Q8: RN1303.4 (R4.1), U1302.2 (Q0), U1304.2 (A0), U1306.2 (A0)
/tsp/Q9: RN1303.3 (R3.1), U1302.19 (Q7), U1304.3 (A1), U1306.3 (A1)
/tsp/Q10: RN1303.2 (R2.1), U1302.5 (Q1), U1304.4 (A2), U1306.4 (A2)
/tsp/Q11: RN1303.1 (R1.1), U1302.16 (Q6), U1304.5 (A3), U1306.5 (A3)
/tsp/Q12: RN1304.4 (R4.1), U1302.6 (Q2), U1304.6 (A4), U1306.6 (A4)
/tsp/Q13: RN1304.3 (R3.1), U1302.15 (Q5), U1304.7 (A5), U1306.7 (A5)
/tsp/Q14: RN1304.2 (R2.1), U1302.9 (Q3), U1304.8 (A6), U1306.8 (A6)
/tsp/Q15: RN1304.1 (R1.1), U1302.12 (Q4), U1304.9 (A7), U1306.9 (A7)
BUSA0: U303.11 (Y7), U403.11 (Y7), U503.11 (Y7), U603.11 (Y7), U703.11 (Y7), U803.11 (Y7), U903.11 (Y7), U1003.11 (Y7), U1103.11 (Y7), U1203.11 (Y7), U1303.11 (Y7), U1403.11 (Y7); also elsewhere on the board
BUSA1: U303.12 (Y6), U403.12 (Y6), U503.12 (Y6), U603.12 (Y6), U703.12 (Y6), U803.12 (Y6), U903.12 (Y6), U1003.12 (Y6), U1103.12 (Y6), U1203.12 (Y6), U1303.12 (Y6), U1403.12 (Y6); also elsewhere on the board
BUSA2: U303.13 (Y5), U403.13 (Y5), U503.13 (Y5), U603.13 (Y5), U703.13 (Y5), U803.13 (Y5), U903.13 (Y5), U1003.13 (Y5), U1103.13 (Y5), U1203.13 (Y5), U1303.13 (Y5), U1403.13 (Y5); also elsewhere on the board
BUSA3: U303.14 (Y4), U403.14 (Y4), U503.14 (Y4), U603.14 (Y4), U703.14 (Y4), U803.14 (Y4), U903.14 (Y4), U1003.14 (Y4), U1103.14 (Y4), U1203.14 (Y4), U1303.14 (Y4), U1403.14 (Y4); also elsewhere on the board
BUSA4: U303.15 (Y3), U403.15 (Y3), U503.15 (Y3), U603.15 (Y3), U703.15 (Y3), U803.15 (Y3), U903.15 (Y3), U1003.15 (Y3), U1103.15 (Y3), U1203.15 (Y3), U1303.15 (Y3), U1403.15 (Y3); also elsewhere on the board
BUSA5: U303.16 (Y2), U403.16 (Y2), U503.16 (Y2), U603.16 (Y2), U703.16 (Y2), U803.16 (Y2), U903.16 (Y2), U1003.16 (Y2), U1103.16 (Y2), U1203.16 (Y2), U1303.16 (Y2), U1403.16 (Y2); also elsewhere on the board
BUSA6: U303.17 (Y1), U403.17 (Y1), U503.17 (Y1), U603.17 (Y1), U703.17 (Y1), U803.17 (Y1), U903.17 (Y1), U1003.17 (Y1), U1103.17 (Y1), U1203.17 (Y1), U1303.17 (Y1), U1403.17 (Y1); also elsewhere on the board
BUSA7: U303.18 (Y0), U403.18 (Y0), U503.18 (Y0), U603.18 (Y0), U703.18 (Y0), U803.18 (Y0), U903.18 (Y0), U1003.18 (Y0), U1103.18 (Y0), U1203.18 (Y0), U1303.18 (Y0), U1403.18 (Y0); also elsewhere on the board
BUSA8: U304.18 (Y0), U404.18 (Y0), U504.18 (Y0), U604.18 (Y0), U704.18 (Y0), U804.18 (Y0), U904.18 (Y0), U1004.18 (Y0), U1104.18 (Y0), U1204.18 (Y0), U1304.18 (Y0), U1404.18 (Y0); also elsewhere on the board
BUSA9: U304.17 (Y1), U404.17 (Y1), U504.17 (Y1), U604.17 (Y1), U704.17 (Y1), U804.17 (Y1), U904.17 (Y1), U1004.17 (Y1), U1104.17 (Y1), U1204.17 (Y1), U1304.17 (Y1), U1404.17 (Y1); also elsewhere on the board
BUSA10: U304.16 (Y2), U404.16 (Y2), U504.16 (Y2), U604.16 (Y2), U704.16 (Y2), U804.16 (Y2), U904.16 (Y2), U1004.16 (Y2), U1104.16 (Y2), U1204.16 (Y2), U1304.16 (Y2), U1404.16 (Y2); also elsewhere on the board
BUSA11: U304.15 (Y3), U404.15 (Y3), U504.15 (Y3), U604.15 (Y3), U704.15 (Y3), U804.15 (Y3), U904.15 (Y3), U1004.15 (Y3), U1104.15 (Y3), U1204.15 (Y3), U1304.15 (Y3), U1404.15 (Y3); also elsewhere on the board
BUSA12: U304.14 (Y4), U404.14 (Y4), U504.14 (Y4), U604.14 (Y4), U704.14 (Y4), U804.14 (Y4), U904.14 (Y4), U1004.14 (Y4), U1104.14 (Y4), U1204.14 (Y4), U1304.14 (Y4), U1404.14 (Y4); also elsewhere on the board
BUSA13: U304.13 (Y5), U404.13 (Y5), U504.13 (Y5), U604.13 (Y5), U704.13 (Y5), U804.13 (Y5), U904.13 (Y5), U1004.13 (Y5), U1104.13 (Y5), U1204.13 (Y5), U1304.13 (Y5), U1404.13 (Y5); also elsewhere on the board
BUSA14: U304.12 (Y6), U404.12 (Y6), U504.12 (Y6), U604.12 (Y6), U704.12 (Y6), U804.12 (Y6), U904.12 (Y6), U1004.12 (Y6), U1104.12 (Y6), U1204.12 (Y6), U1304.12 (Y6), U1404.12 (Y6); also elsewhere on the board
BUSA15: U304.11 (Y7), U404.11 (Y7), U504.11 (Y7), U604.11 (Y7), U704.11 (Y7), U804.11 (Y7), U904.11 (Y7), U1004.11 (Y7), U1104.11 (Y7), U1204.11 (Y7), U1304.11 (Y7), U1404.11 (Y7); also elsewhere on the board
BUSB0: U305.11 (Y7), U405.11 (Y7), U505.11 (Y7), U605.11 (Y7), U705.11 (Y7), U805.11 (Y7), U905.11 (Y7), U1005.11 (Y7), U1105.11 (Y7), U1205.11 (Y7), U1305.11 (Y7), U1405.11 (Y7); also elsewhere on the board
BUSB1: U305.12 (Y6), U405.12 (Y6), U505.12 (Y6), U605.12 (Y6), U705.12 (Y6), U805.12 (Y6), U905.12 (Y6), U1005.12 (Y6), U1105.12 (Y6), U1205.12 (Y6), U1305.12 (Y6), U1405.12 (Y6); also elsewhere on the board
BUSB2: U305.13 (Y5), U405.13 (Y5), U505.13 (Y5), U605.13 (Y5), U705.13 (Y5), U805.13 (Y5), U905.13 (Y5), U1005.13 (Y5), U1105.13 (Y5), U1205.13 (Y5), U1305.13 (Y5), U1405.13 (Y5); also elsewhere on the board
BUSB3: U305.14 (Y4), U405.14 (Y4), U505.14 (Y4), U605.14 (Y4), U705.14 (Y4), U805.14 (Y4), U905.14 (Y4), U1005.14 (Y4), U1105.14 (Y4), U1205.14 (Y4), U1305.14 (Y4), U1405.14 (Y4); also elsewhere on the board
BUSB4: U305.15 (Y3), U405.15 (Y3), U505.15 (Y3), U605.15 (Y3), U705.15 (Y3), U805.15 (Y3), U905.15 (Y3), U1005.15 (Y3), U1105.15 (Y3), U1205.15 (Y3), U1305.15 (Y3), U1405.15 (Y3); also elsewhere on the board
BUSB5: U305.16 (Y2), U405.16 (Y2), U505.16 (Y2), U605.16 (Y2), U705.16 (Y2), U805.16 (Y2), U905.16 (Y2), U1005.16 (Y2), U1105.16 (Y2), U1205.16 (Y2), U1305.16 (Y2), U1405.16 (Y2); also elsewhere on the board
BUSB6: U305.17 (Y1), U405.17 (Y1), U505.17 (Y1), U605.17 (Y1), U705.17 (Y1), U805.17 (Y1), U905.17 (Y1), U1005.17 (Y1), U1105.17 (Y1), U1205.17 (Y1), U1305.17 (Y1), U1405.17 (Y1); also elsewhere on the board
BUSB7: U305.18 (Y0), U405.18 (Y0), U505.18 (Y0), U605.18 (Y0), U705.18 (Y0), U805.18 (Y0), U905.18 (Y0), U1005.18 (Y0), U1105.18 (Y0), U1205.18 (Y0), U1305.18 (Y0), U1405.18 (Y0); also elsewhere on the board
BUSB8: U306.18 (Y0), U406.18 (Y0), U506.18 (Y0), U606.18 (Y0), U706.18 (Y0), U806.18 (Y0), U906.18 (Y0), U1006.18 (Y0), U1106.18 (Y0), U1206.18 (Y0), U1306.18 (Y0), U1406.18 (Y0); also elsewhere on the board
BUSB9: U306.17 (Y1), U406.17 (Y1), U506.17 (Y1), U606.17 (Y1), U706.17 (Y1), U806.17 (Y1), U906.17 (Y1), U1006.17 (Y1), U1106.17 (Y1), U1206.17 (Y1), U1306.17 (Y1), U1406.17 (Y1); also elsewhere on the board
BUSB10: U306.16 (Y2), U406.16 (Y2), U506.16 (Y2), U606.16 (Y2), U706.16 (Y2), U806.16 (Y2), U906.16 (Y2), U1006.16 (Y2), U1106.16 (Y2), U1206.16 (Y2), U1306.16 (Y2), U1406.16 (Y2); also elsewhere on the board
BUSB11: U306.15 (Y3), U406.15 (Y3), U506.15 (Y3), U606.15 (Y3), U706.15 (Y3), U806.15 (Y3), U906.15 (Y3), U1006.15 (Y3), U1106.15 (Y3), U1206.15 (Y3), U1306.15 (Y3), U1406.15 (Y3); also elsewhere on the board
BUSB12: U306.14 (Y4), U406.14 (Y4), U506.14 (Y4), U606.14 (Y4), U706.14 (Y4), U806.14 (Y4), U906.14 (Y4), U1006.14 (Y4), U1106.14 (Y4), U1206.14 (Y4), U1306.14 (Y4), U1406.14 (Y4); also elsewhere on the board
BUSB13: U306.13 (Y5), U406.13 (Y5), U506.13 (Y5), U606.13 (Y5), U706.13 (Y5), U806.13 (Y5), U906.13 (Y5), U1006.13 (Y5), U1106.13 (Y5), U1206.13 (Y5), U1306.13 (Y5), U1406.13 (Y5); also elsewhere on the board
BUSB14: U306.12 (Y6), U406.12 (Y6), U506.12 (Y6), U606.12 (Y6), U706.12 (Y6), U806.12 (Y6), U906.12 (Y6), U1006.12 (Y6), U1106.12 (Y6), U1206.12 (Y6), U1306.12 (Y6), U1406.12 (Y6); also elsewhere on the board
BUSB15: U306.11 (Y7), U406.11 (Y7), U506.11 (Y7), U606.11 (Y7), U706.11 (Y7), U806.11 (Y7), U906.11 (Y7), U1006.11 (Y7), U1106.11 (Y7), U1206.11 (Y7), U1306.11 (Y7), U1406.11 (Y7); also elsewhere on the board
DATAINT0: U301.8 (D3), U401.8 (D3), U501.8 (D3), U601.8 (D3), U701.8 (D3), U801.8 (D3), U901.8 (D3), U1001.8 (D3), U1101.8 (D3), U1201.8 (D3), U1301.8 (D3), U1401.8 (D3); also elsewhere on the board
DATAINT1: U301.13 (D4), U401.13 (D4), U501.13 (D4), U601.13 (D4), U701.13 (D4), U801.13 (D4), U901.13 (D4), U1001.13 (D4), U1101.13 (D4), U1201.13 (D4), U1301.13 (D4), U1401.13 (D4); also elsewhere on the board
DATAINT2: U301.7 (D2), U401.7 (D2), U501.7 (D2), U601.7 (D2), U701.7 (D2), U801.7 (D2), U901.7 (D2), U1001.7 (D2), U1101.7 (D2), U1201.7 (D2), U1301.7 (D2), U1401.7 (D2); also elsewhere on the board
DATAINT3: U301.14 (D5), U401.14 (D5), U501.14 (D5), U601.14 (D5), U701.14 (D5), U801.14 (D5), U901.14 (D5), U1001.14 (D5), U1101.14 (D5), U1201.14 (D5), U1301.14 (D5), U1401.14 (D5); also elsewhere on the board
DATAINT4: U301.4 (D1), U401.4 (D1), U501.4 (D1), U601.4 (D1), U701.4 (D1), U801.4 (D1), U901.4 (D1), U1001.4 (D1), U1101.4 (D1), U1201.4 (D1), U1301.4 (D1), U1401.4 (D1); also elsewhere on the board
DATAINT5: U301.17 (D6), U401.17 (D6), U501.17 (D6), U601.17 (D6), U701.17 (D6), U801.17 (D6), U901.17 (D6), U1001.17 (D6), U1101.17 (D6), U1201.17 (D6), U1301.17 (D6), U1401.17 (D6); also elsewhere on the board
DATAINT6: U301.3 (D0), U401.3 (D0), U501.3 (D0), U601.3 (D0), U701.3 (D0), U801.3 (D0), U901.3 (D0), U1001.3 (D0), U1101.3 (D0), U1201.3 (D0), U1301.3 (D0), U1401.3 (D0); also elsewhere on the board
DATAINT7: U301.18 (D7), U401.18 (D7), U501.18 (D7), U601.18 (D7), U701.18 (D7), U801.18 (D7), U901.18 (D7), U1001.18 (D7), U1101.18 (D7), U1201.18 (D7), U1301.18 (D7), U1401.18 (D7); also elsewhere on the board
DATAINT8: U302.3 (D0), U402.3 (D0), U502.3 (D0), U602.3 (D0), U702.3 (D0), U802.3 (D0), U902.3 (D0), U1002.3 (D0), U1102.3 (D0), U1202.3 (D0), U1302.3 (D0), U1402.3 (D0); also elsewhere on the board
DATAINT9: U302.18 (D7), U402.18 (D7), U502.18 (D7), U602.18 (D7), U702.18 (D7), U802.18 (D7), U902.18 (D7), U1002.18 (D7), U1102.18 (D7), U1202.18 (D7), U1302.18 (D7), U1402.18 (D7); also elsewhere on the board
DATAINT10: U302.4 (D1), U402.4 (D1), U502.4 (D1), U602.4 (D1), U702.4 (D1), U802.4 (D1), U902.4 (D1), U1002.4 (D1), U1102.4 (D1), U1202.4 (D1), U1302.4 (D1), U1402.4 (D1); also elsewhere on the board
DATAINT11: U302.17 (D6), U402.17 (D6), U502.17 (D6), U602.17 (D6), U702.17 (D6), U802.17 (D6), U902.17 (D6), U1002.17 (D6), U1102.17 (D6), U1202.17 (D6), U1302.17 (D6), U1402.17 (D6); also elsewhere on the board
DATAINT12: U302.7 (D2), U402.7 (D2), U502.7 (D2), U602.7 (D2), U702.7 (D2), U802.7 (D2), U902.7 (D2), U1002.7 (D2), U1102.7 (D2), U1202.7 (D2), U1302.7 (D2), U1402.7 (D2); also elsewhere on the board
DATAINT13: U302.14 (D5), U402.14 (D5), U502.14 (D5), U602.14 (D5), U702.14 (D5), U802.14 (D5), U902.14 (D5), U1002.14 (D5), U1102.14 (D5), U1202.14 (D5), U1302.14 (D5), U1402.14 (D5); also elsewhere on the board
DATAINT14: U302.8 (D3), U402.8 (D3), U502.8 (D3), U602.8 (D3), U702.8 (D3), U802.8 (D3), U902.8 (D3), U1002.8 (D3), U1102.8 (D3), U1202.8 (D3), U1302.8 (D3), U1402.8 (D3); also elsewhere on the board
DATAINT15: U302.13 (D4), U402.13 (D4), U502.13 (D4), U602.13 (D4), U702.13 (D4), U802.13 (D4), U902.13 (D4), U1002.13 (D4), U1102.13 (D4), U1202.13 (D4), U1302.13 (D4), U1402.13 (D4); also elsewhere on the board
GND: C301.1, C302.1, C303.1, C304.1, C305.1, C306.1, C401.1, C402.1, C403.1, C404.1, C405.1, C406.1, C501.1, C502.1, C503.1, C504.1, C505.1, C506.1, C601.1, C602.1, C603.1, C604.1, C605.1, C606.1, C701.1, C702.1, C703.1, C704.1, C705.1, C706.1, C801.1, C802.1, C803.1, C804.1, C805.1, C806.1, C901.1, C902.1, C903.1, C904.1, C905.1, C906.1, C1001.1, C1002.1, C1003.1, C1004.1, C1005.1, C1006.1, C1101.1, C1102.1, C1103.1, C1104.1, C1105.1, C1106.1, C1201.1, C1202.1, C1203.1, C1204.1, C1205.1, C1206.1, C1301.1, C1302.1, C1303.1, C1304.1, C1305.1, C1306.1, C1401.1, C1402.1, C1403.1, C1404.1, C1405.1, C1406.1, D304.1 (K), D305.1 (K), D306.1 (K), D307.1 (K), D308.1 (K), D309.1 (K), D310.1 (K), D311.1 (K)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; also elsewhere on the board
unnamed: D301.2 (A), R301.2
unnamed: D302.2 (A), R302.2
unnamed: D303.2 (A), R303.2
unnamed: D304.2 (A), RN301.8 (R1.2)
unnamed: D305.2 (A), RN301.7 (R2.2)
unnamed: D306.2 (A), RN301.6 (R3.2)
unnamed: D307.2 (A), RN301.5 (R4.2)
unnamed: D308.2 (A), RN302.8 (R1.2)
unnamed: D309.2 (A), RN302.7 (R2.2)
unnamed: D310.2 (A), RN302.6 (R3.2)
unnamed: D311.2 (A), RN302.5 (R4.2)
unnamed: D312.2 (A), RN303.8 (R1.2)
unnamed: D313.2 (A), RN303.7 (R2.2)
unnamed: D314.2 (A), RN303.6 (R3.2)
unnamed: D315.2 (A), RN303.5 (R4.2)
unnamed: D316.2 (A), RN304.8 (R1.2)
unnamed: D317.2 (A), RN304.7 (R2.2)
unnamed: D318.2 (A), RN304.6 (R3.2)
unnamed: D319.2 (A), RN304.5 (R4.2)
unnamed: D401.2 (A), R401.2
unnamed: D402.2 (A), R402.2
unnamed: D403.2 (A), R403.2
unnamed: D404.2 (A), RN401.8 (R1.2)
unnamed: D405.2 (A), RN401.7 (R2.2)
unnamed: D406.2 (A), RN401.6 (R3.2)
unnamed: D407.2 (A), RN401.5 (R4.2)
unnamed: D408.2 (A), RN402.8 (R1.2)
unnamed: D409.2 (A), RN402.7 (R2.2)
unnamed: D410.2 (A), RN402.6 (R3.2)
unnamed: D411.2 (A), RN402.5 (R4.2)
unnamed: D412.2 (A), RN403.8 (R1.2)
unnamed: D413.2 (A), RN403.7 (R2.2)
unnamed: D414.2 (A), RN403.6 (R3.2)
unnamed: D415.2 (A), RN403.5 (R4.2)
unnamed: D416.2 (A), RN404.8 (R1.2)
unnamed: D417.2 (A), RN404.7 (R2.2)
unnamed: D418.2 (A), RN404.6 (R3.2)
unnamed: D419.2 (A), RN404.5 (R4.2)
unnamed: D501.2 (A), R501.2
unnamed: D502.2 (A), R502.2
unnamed: D503.2 (A), R503.2
unnamed: D504.2 (A), RN501.8 (R1.2)
unnamed: D505.2 (A), RN501.7 (R2.2)
unnamed: D506.2 (A), RN501.6 (R3.2)
unnamed: D507.2 (A), RN501.5 (R4.2)
unnamed: D508.2 (A), RN502.8 (R1.2)
unnamed: D509.2 (A), RN502.7 (R2.2)
unnamed: D510.2 (A), RN502.6 (R3.2)
unnamed: D511.2 (A), RN502.5 (R4.2)
unnamed: D512.2 (A), RN503.8 (R1.2)
unnamed: D513.2 (A), RN503.7 (R2.2)
unnamed: D514.2 (A), RN503.6 (R3.2)
unnamed: D515.2 (A), RN503.5 (R4.2)
unnamed: D516.2 (A), RN504.8 (R1.2)
unnamed: D517.2 (A), RN504.7 (R2.2)
unnamed: D518.2 (A), RN504.6 (R3.2)
unnamed: D519.2 (A), RN504.5 (R4.2)
unnamed: D601.2 (A), R601.2
unnamed: D602.2 (A), R602.2
unnamed: D603.2 (A), R603.2
unnamed: D604.2 (A), RN601.8 (R1.2)
unnamed: D605.2 (A), RN601.7 (R2.2)
unnamed: D606.2 (A), RN601.6 (R3.2)
unnamed: D607.2 (A), RN601.5 (R4.2)
unnamed: D608.2 (A), RN602.8 (R1.2)
unnamed: D609.2 (A), RN602.7 (R2.2)
unnamed: D610.2 (A), RN602.6 (R3.2)
unnamed: D611.2 (A), RN602.5 (R4.2)
unnamed: D612.2 (A), RN603.8 (R1.2)
unnamed: D613.2 (A), RN603.7 (R2.2)
unnamed: D614.2 (A), RN603.6 (R3.2)
unnamed: D615.2 (A), RN603.5 (R4.2)
unnamed: D616.2 (A), RN604.8 (R1.2)
unnamed: D617.2 (A), RN604.7 (R2.2)
unnamed: D618.2 (A), RN604.6 (R3.2)
unnamed: D619.2 (A), RN604.5 (R4.2)
unnamed: D701.2 (A), R701.2
unnamed: D702.2 (A), R702.2
unnamed: D703.2 (A), R703.2
unnamed: D704.2 (A), RN701.8 (R1.2)
unnamed: D705.2 (A), RN701.7 (R2.2)
unnamed: D706.2 (A), RN701.6 (R3.2)
unnamed: D707.2 (A), RN701.5 (R4.2)
unnamed: D708.2 (A), RN702.8 (R1.2)
unnamed: D709.2 (A), RN702.7 (R2.2)
unnamed: D710.2 (A), RN702.6 (R3.2)
unnamed: D711.2 (A), RN702.5 (R4.2)
unnamed: D712.2 (A), RN703.8 (R1.2)
unnamed: D713.2 (A), RN703.7 (R2.2)
unnamed: D714.2 (A), RN703.6 (R3.2)
unnamed: D715.2 (A), RN703.5 (R4.2)
unnamed: D716.2 (A), RN704.8 (R1.2)
unnamed: D717.2 (A), RN704.7 (R2.2)
unnamed: D718.2 (A), RN704.6 (R3.2)
unnamed: D719.2 (A), RN704.5 (R4.2)
unnamed: D801.2 (A), R801.2
unnamed: D802.2 (A), R802.2
unnamed: D803.2 (A), R803.2
unnamed: D804.2 (A), RN801.8 (R1.2)
unnamed: D805.2 (A), RN801.7 (R2.2)
unnamed: D806.2 (A), RN801.6 (R3.2)
unnamed: D807.2 (A), RN801.5 (R4.2)
unnamed: D808.2 (A), RN802.8 (R1.2)
unnamed: D809.2 (A), RN802.7 (R2.2)
unnamed: D810.2 (A), RN802.6 (R3.2)
unnamed: D811.2 (A), RN802.5 (R4.2)
unnamed: D812.2 (A), RN803.8 (R1.2)
unnamed: D813.2 (A), RN803.7 (R2.2)
unnamed: D814.2 (A), RN803.6 (R3.2)
unnamed: D815.2 (A), RN803.5 (R4.2)
unnamed: D816.2 (A), RN804.8 (R1.2)
unnamed: D817.2 (A), RN804.7 (R2.2)
unnamed: D818.2 (A), RN804.6 (R3.2)
unnamed: D819.2 (A), RN804.5 (R4.2)
unnamed: D901.2 (A), R901.2
unnamed: D902.2 (A), R902.2
unnamed: D903.2 (A), R903.2
unnamed: D904.2 (A), RN901.8 (R1.2)
unnamed: D905.2 (A), RN901.7 (R2.2)
unnamed: D906.2 (A), RN901.6 (R3.2)
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
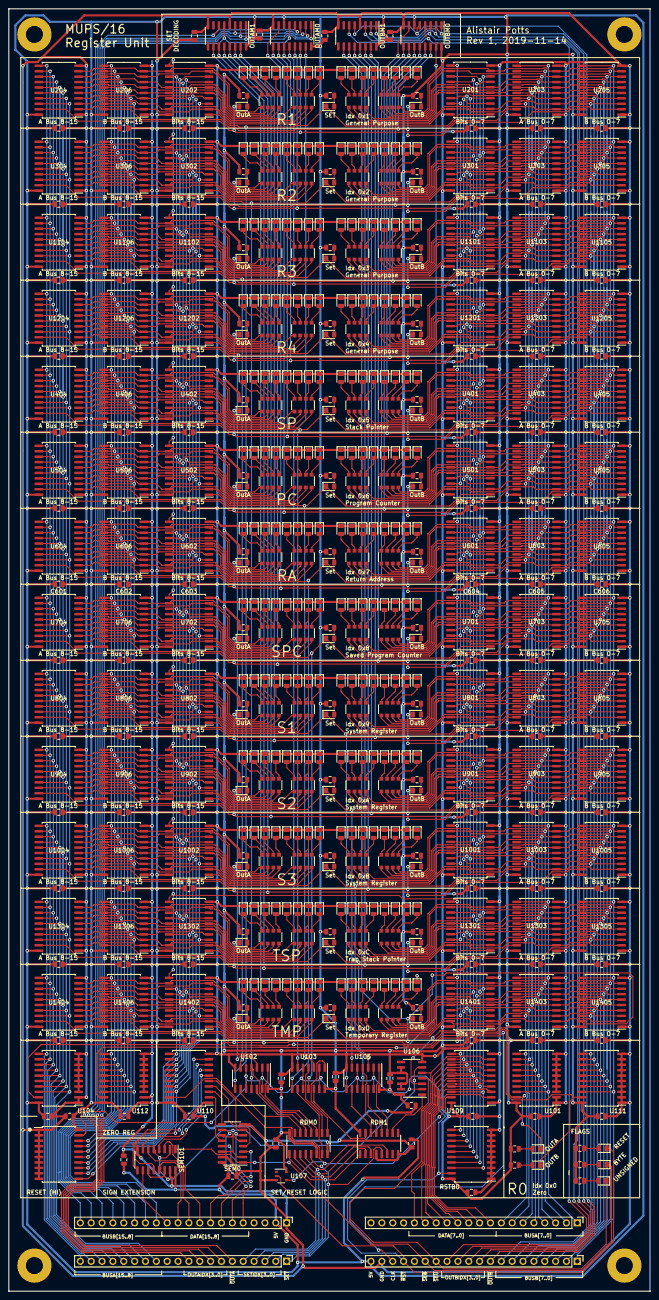
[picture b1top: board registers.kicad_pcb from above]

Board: 2 copper layers, 150.0 x 300.0 mm, 553 parts (0 on the bottom side), 609 nets.
